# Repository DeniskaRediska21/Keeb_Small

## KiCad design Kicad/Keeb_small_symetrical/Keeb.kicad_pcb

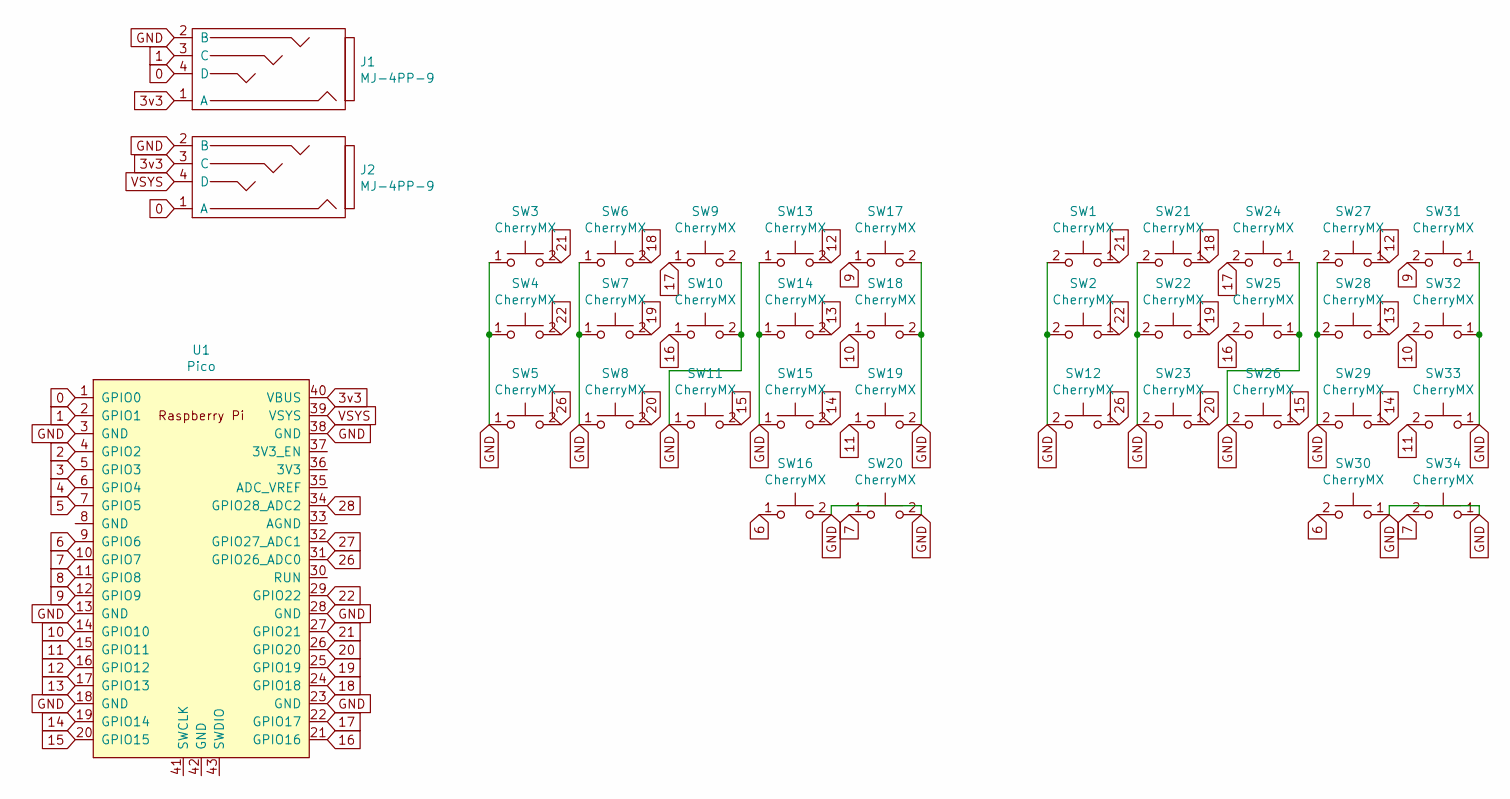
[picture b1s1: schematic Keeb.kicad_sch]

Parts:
J1, J2: MJ-4PP-9
SW1, SW2, SW3, SW4, SW5, SW6, SW7, SW8, SW9, SW10, SW11, SW12, SW13, SW14, SW15, SW16, SW17, SW18, SW19, SW20, SW21, SW22, SW23, SW24, SW25, SW26, SW27, SW28, SW29, SW30, SW31, SW32, SW33, SW34: CherryMX; MX_PCB_1.00u
U1: Pico; RPi_Pico_SMD_TH

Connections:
0: J1.4 (D), J2.1 (A), U1.1 (GPIO0)
1: J1.3 (C), U1.2 (GPIO1)
2: U1.4 (GPIO2)
3: U1.5 (GPIO3)
3v3: J1.1 (A), J2.3 (C), U1.40 (VBUS)
4: U1.6 (GPIO4)
5: U1.7 (GPIO5)
6: SW16.1, SW30.2, U1.9 (GPIO6)
7: SW20.1, SW34.2, U1.10 (GPIO7)
8: U1.11 (GPIO8)
9: SW17.1, SW31.2, U1.12 (GPIO9)
10: SW18.1, SW32.2, U1.14 (GPIO10)
11: SW19.1, SW33.2, U1.15 (GPIO11)
12: SW13.2, SW27.1, U1.16 (GPIO12)
13: SW14.2, SW28.1, U1.17 (GPIO13)
14: SW15.2, SW29.1, U1.19 (GPIO14)
15: SW11.2, SW26.1, U1.20 (GPIO15)
16: SW10.1, SW25.2, U1.21 (GPIO16)
17: SW9.1, SW24.2, U1.22 (GPIO17)
18: SW6.2, SW21.1, U1.24 (GPIO18)
19: SW7.2, SW22.1, U1.25 (GPIO19)
20: SW8.2, SW23.1, U1.26 (GPIO20)
21: SW1.1, SW3.2, U1.27 (GPIO21)
22: SW2.1, SW4.2, U1.29 (GPIO22)
26: SW5.2, SW12.1, U1.31 (GPIO26_ADC0)
27: U1.32 (GPIO27_ADC1)
28: U1.34 (GPIO28_ADC2)
GND: J1.2 (B), J2.2 (B), SW1.2, SW2.2, SW3.1, SW4.1, SW5.1, SW6.1, SW7.1, SW8.1, SW9.2, SW10.2, SW11.1, SW12.2, SW13.1, SW14.1, SW15.1, SW16.2, SW17.2, SW18.2, SW19.2, SW20.2, SW21.2, SW22.2, SW23.2, SW24.1, SW25.1, SW26.2, SW27.2, SW28.2, SW29.2, SW30.1, SW31.1, SW32.1, SW33.1, SW34.1, U1.3 (GND), U1.13 (GND), U1.18 (GND), U1.23 (GND), U1.28 (GND), U1.38 (GND)
VSYS: J2.4 (D), U1.39 (VSYS)

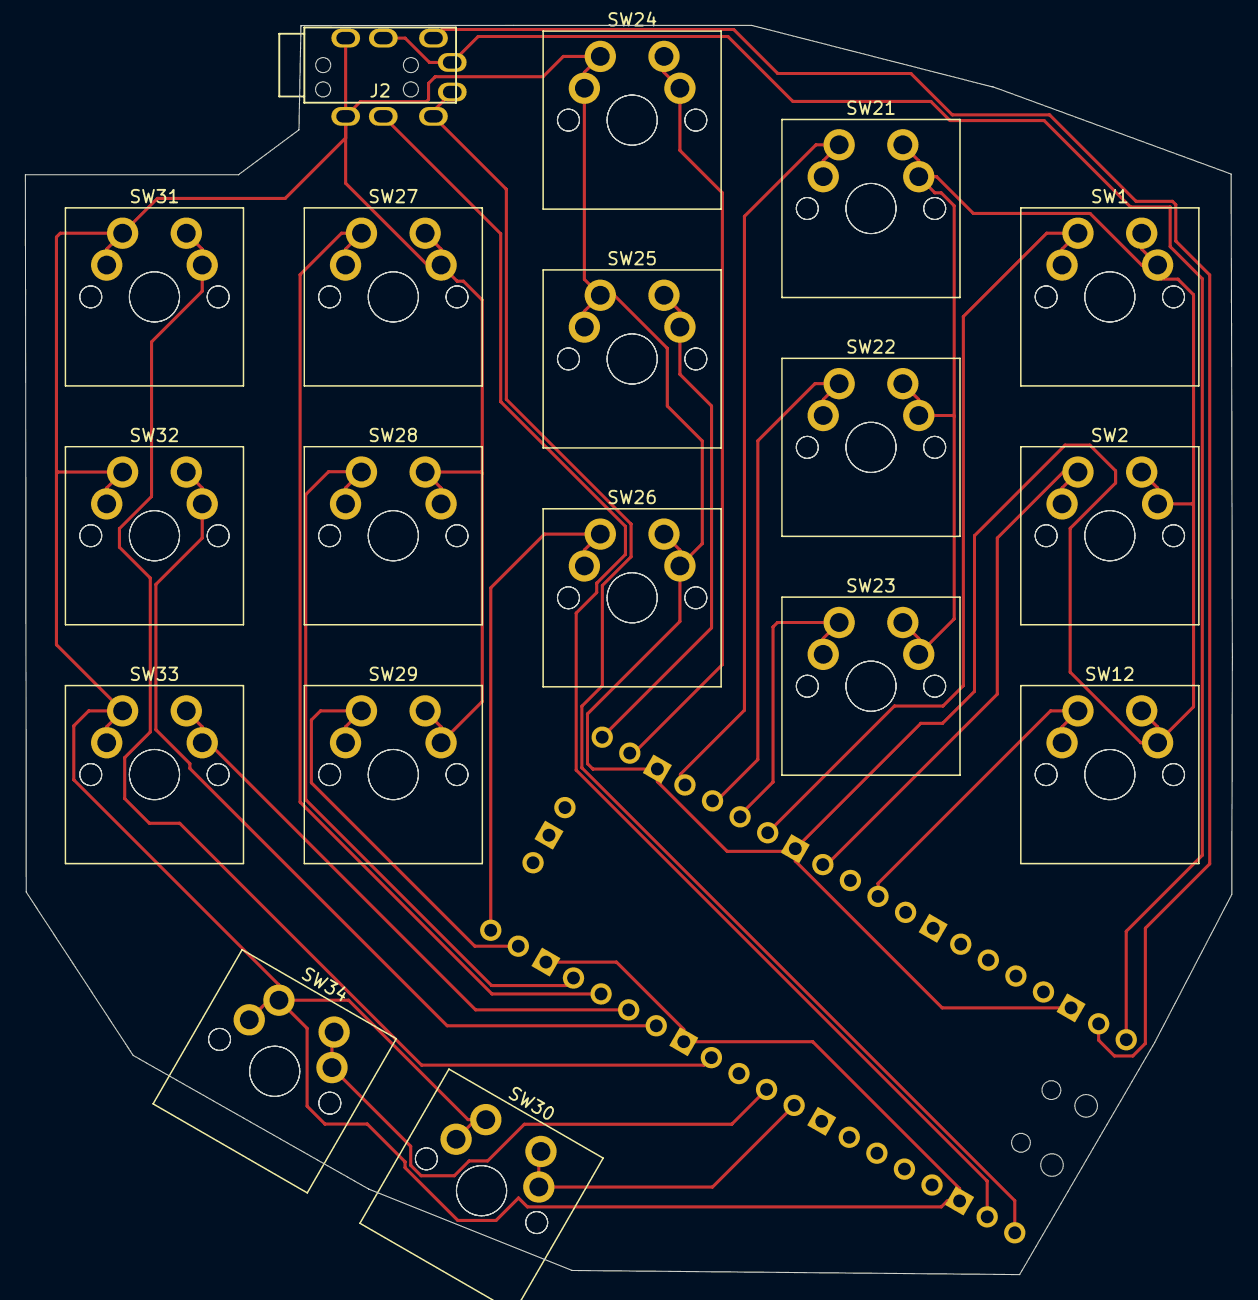
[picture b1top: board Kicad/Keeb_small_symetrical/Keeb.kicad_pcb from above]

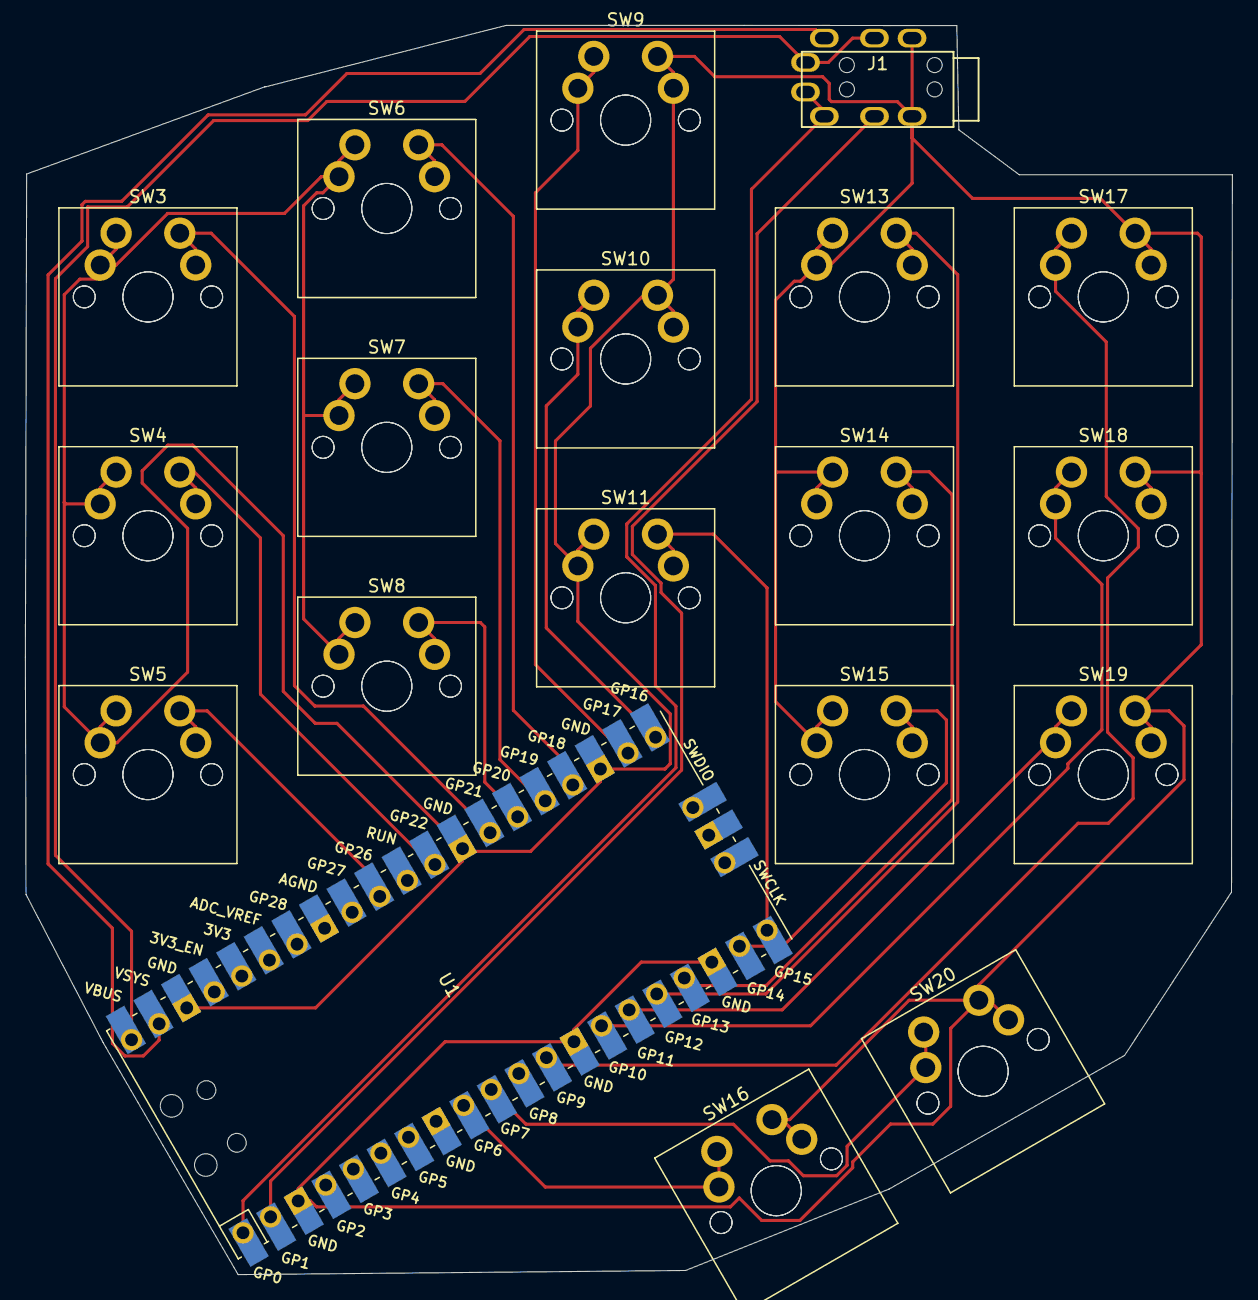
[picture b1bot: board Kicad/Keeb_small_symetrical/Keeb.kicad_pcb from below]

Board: 2 copper layers, 96.3 x 99.6 mm, 37 parts (19 on the bottom side), 22 nets.

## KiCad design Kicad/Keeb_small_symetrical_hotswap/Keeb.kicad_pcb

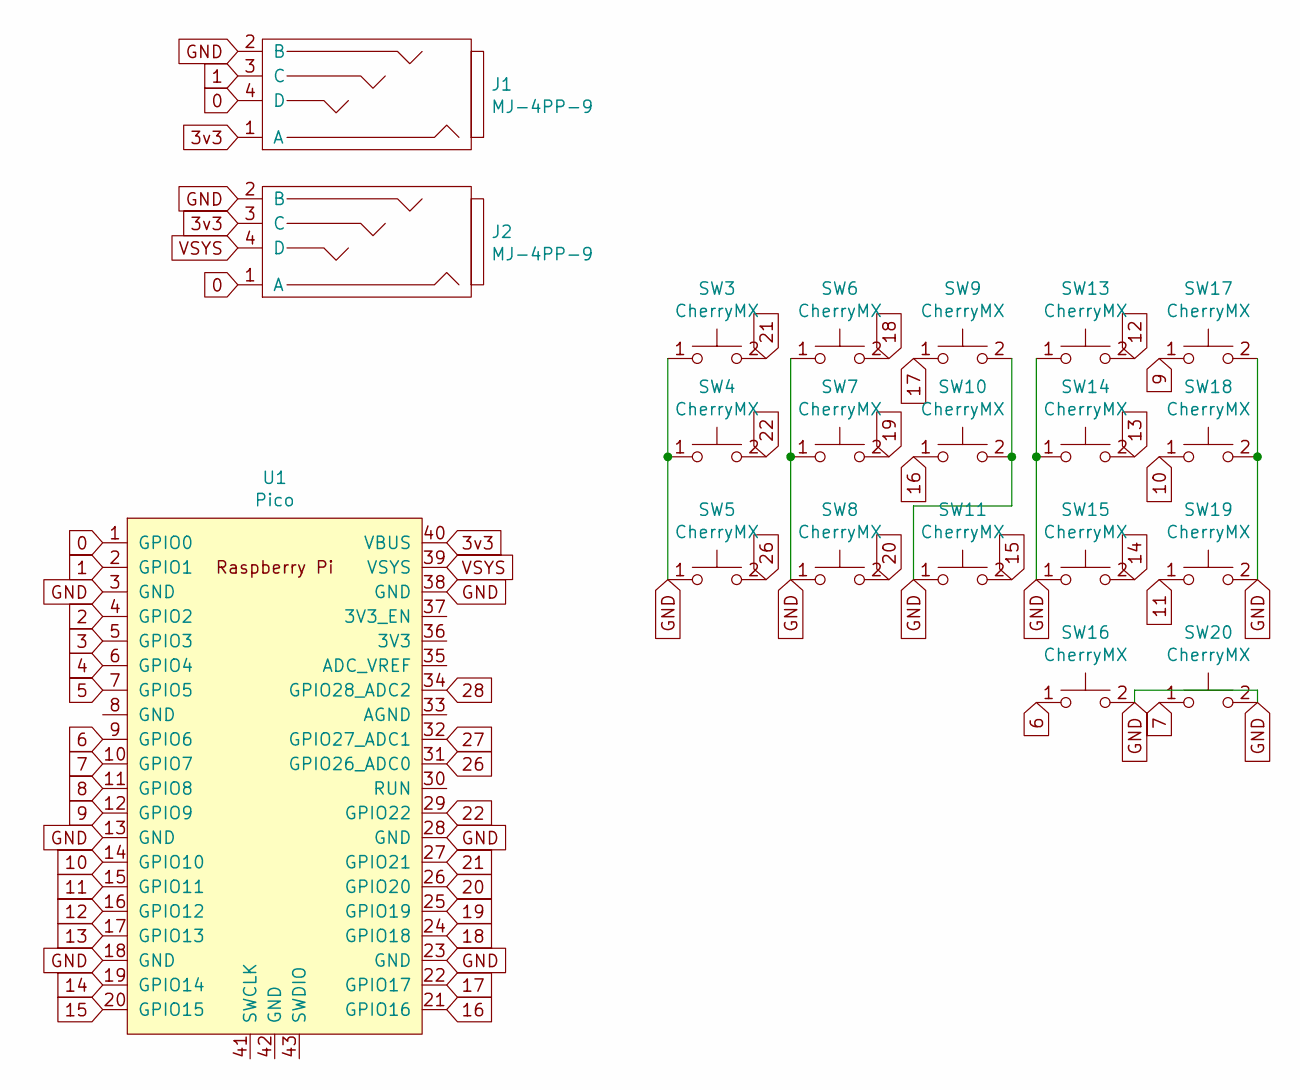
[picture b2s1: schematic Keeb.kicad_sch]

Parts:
J1, J2: MJ-4PP-9
SW3, SW4, SW5, SW6, SW7, SW8, SW9, SW10, SW11, SW13, SW14, SW15, SW16, SW17, SW18, SW19, SW20: CherryMX; Hotswap_MX_1.00u
U1: Pico; RPi_Pico_SMD_TH

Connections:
0: J1.4 (D), J2.1 (A), U1.1 (GPIO0)
1: J1.3 (C), U1.2 (GPIO1)
2: U1.4 (GPIO2)
3: U1.5 (GPIO3)
3v3: J1.1 (A), J2.3 (C), U1.40 (VBUS)
4: U1.6 (GPIO4)
5: U1.7 (GPIO5)
6: SW16.1, U1.9 (GPIO6)
7: SW20.1, U1.10 (GPIO7)
8: U1.11 (GPIO8)
9: SW17.1, U1.12 (GPIO9)
10: SW18.1, U1.14 (GPIO10)
11: SW19.1, U1.15 (GPIO11)
12: SW13.2, U1.16 (GPIO12)
13: SW14.2, U1.17 (GPIO13)
14: SW15.2, U1.19 (GPIO14)
15: SW11.2, U1.20 (GPIO15)
16: SW10.1, U1.21 (GPIO16)
17: SW9.1, U1.22 (GPIO17)
18: SW6.2, U1.24 (GPIO18)
19: SW7.2, U1.25 (GPIO19)
20: SW8.2, U1.26 (GPIO20)
21: SW3.2, U1.27 (GPIO21)
22: SW4.2, U1.29 (GPIO22)
26: SW5.2, U1.31 (GPIO26_ADC0)
27: U1.32 (GPIO27_ADC1)
28: U1.34 (GPIO28_ADC2)
GND: J1.2 (B), J2.2 (B), SW3.1, SW4.1, SW5.1, SW6.1, SW7.1, SW8.1, SW9.2, SW10.2, SW11.1, SW13.1, SW14.1, SW15.1, SW16.2, SW17.2, SW18.2, SW19.2, SW20.2, U1.3 (GND), U1.13 (GND), U1.18 (GND), U1.23 (GND), U1.28 (GND), U1.38 (GND)
VSYS: J2.4 (D), U1.39 (VSYS)

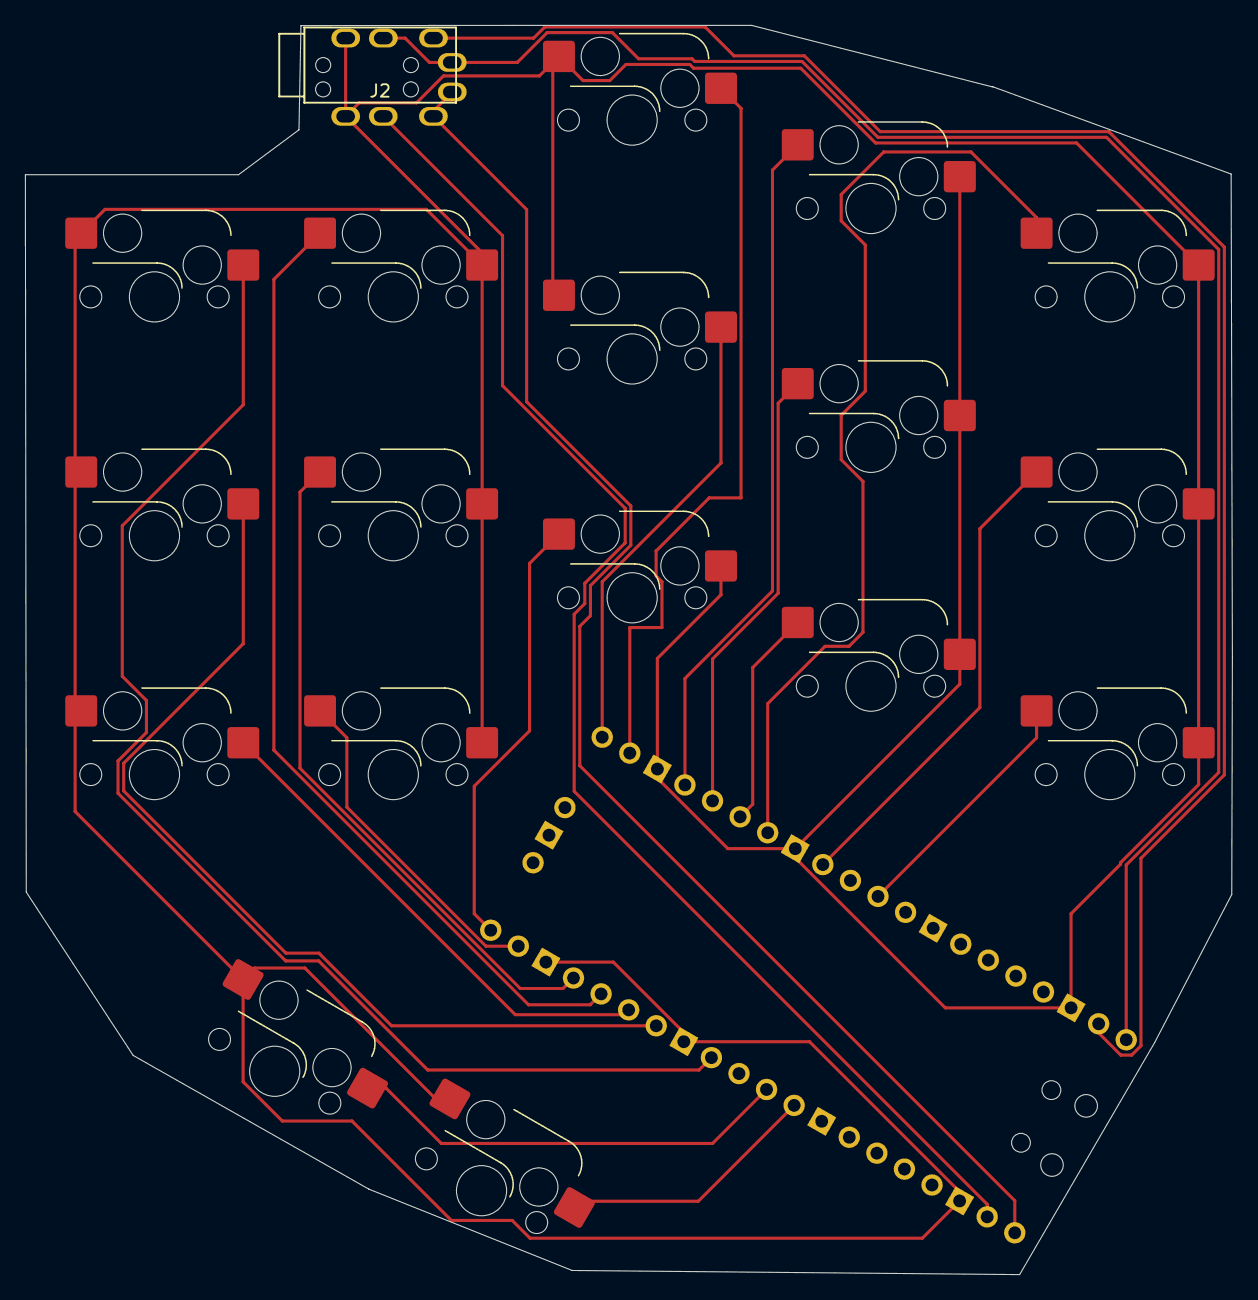
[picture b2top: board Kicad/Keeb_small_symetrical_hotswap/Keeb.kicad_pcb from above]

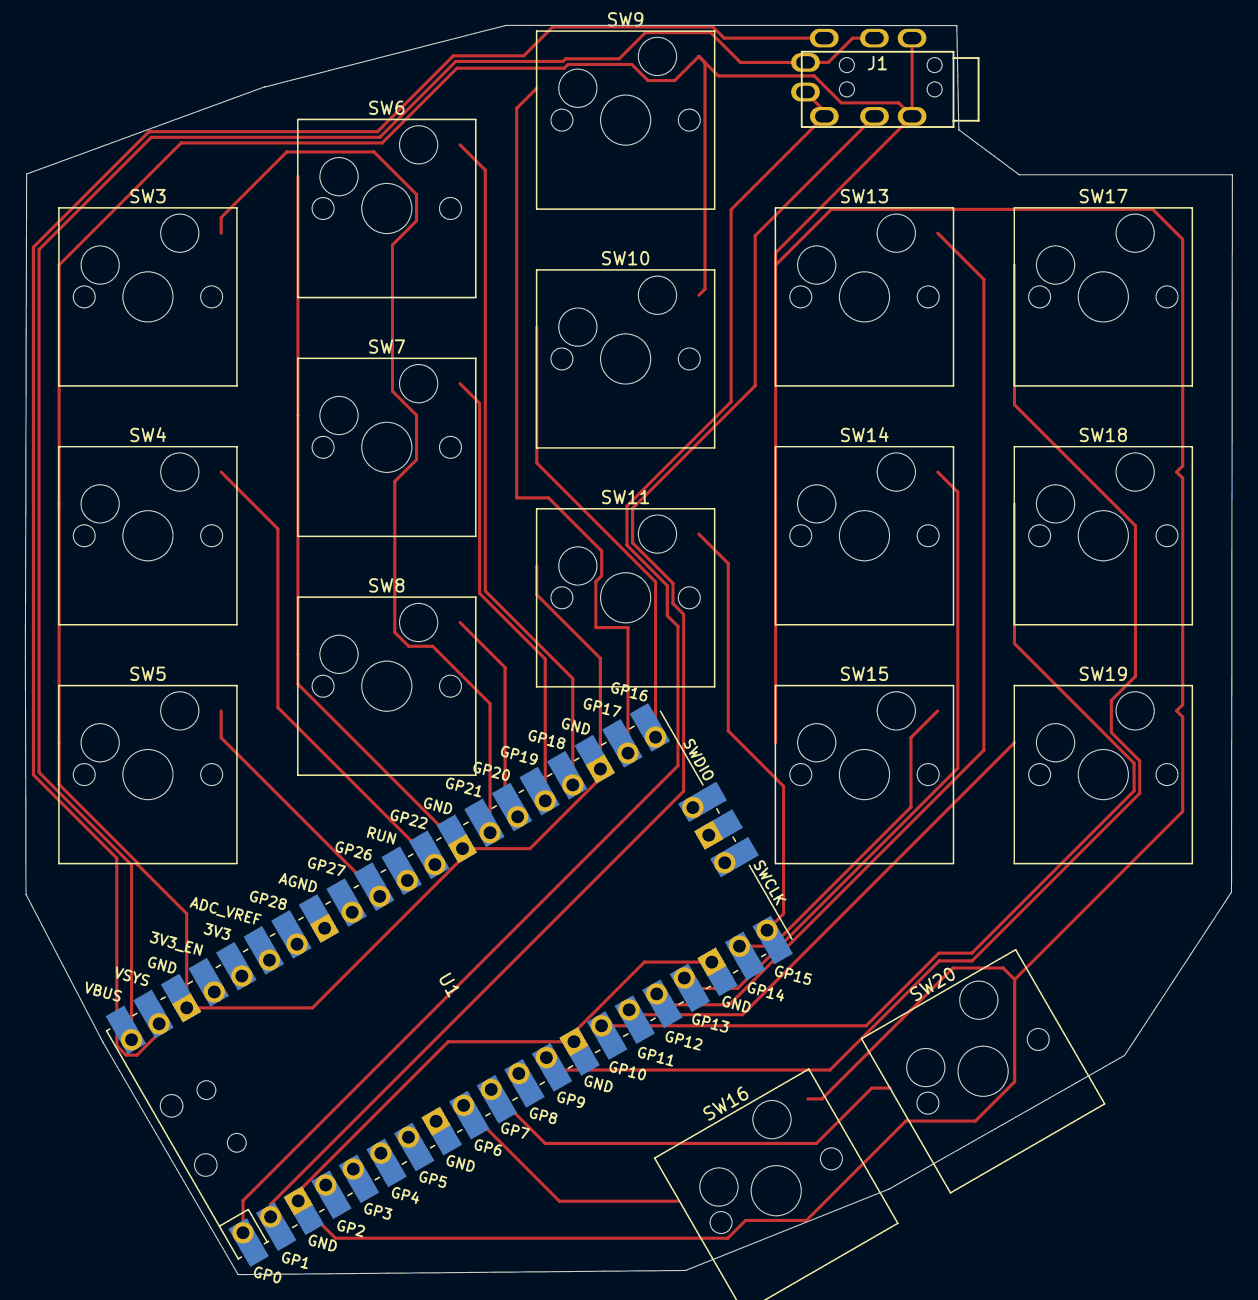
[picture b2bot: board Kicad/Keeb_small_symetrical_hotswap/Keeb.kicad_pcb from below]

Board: 2 copper layers, 96.3 x 99.6 mm, 20 parts (19 on the bottom side), 22 nets.

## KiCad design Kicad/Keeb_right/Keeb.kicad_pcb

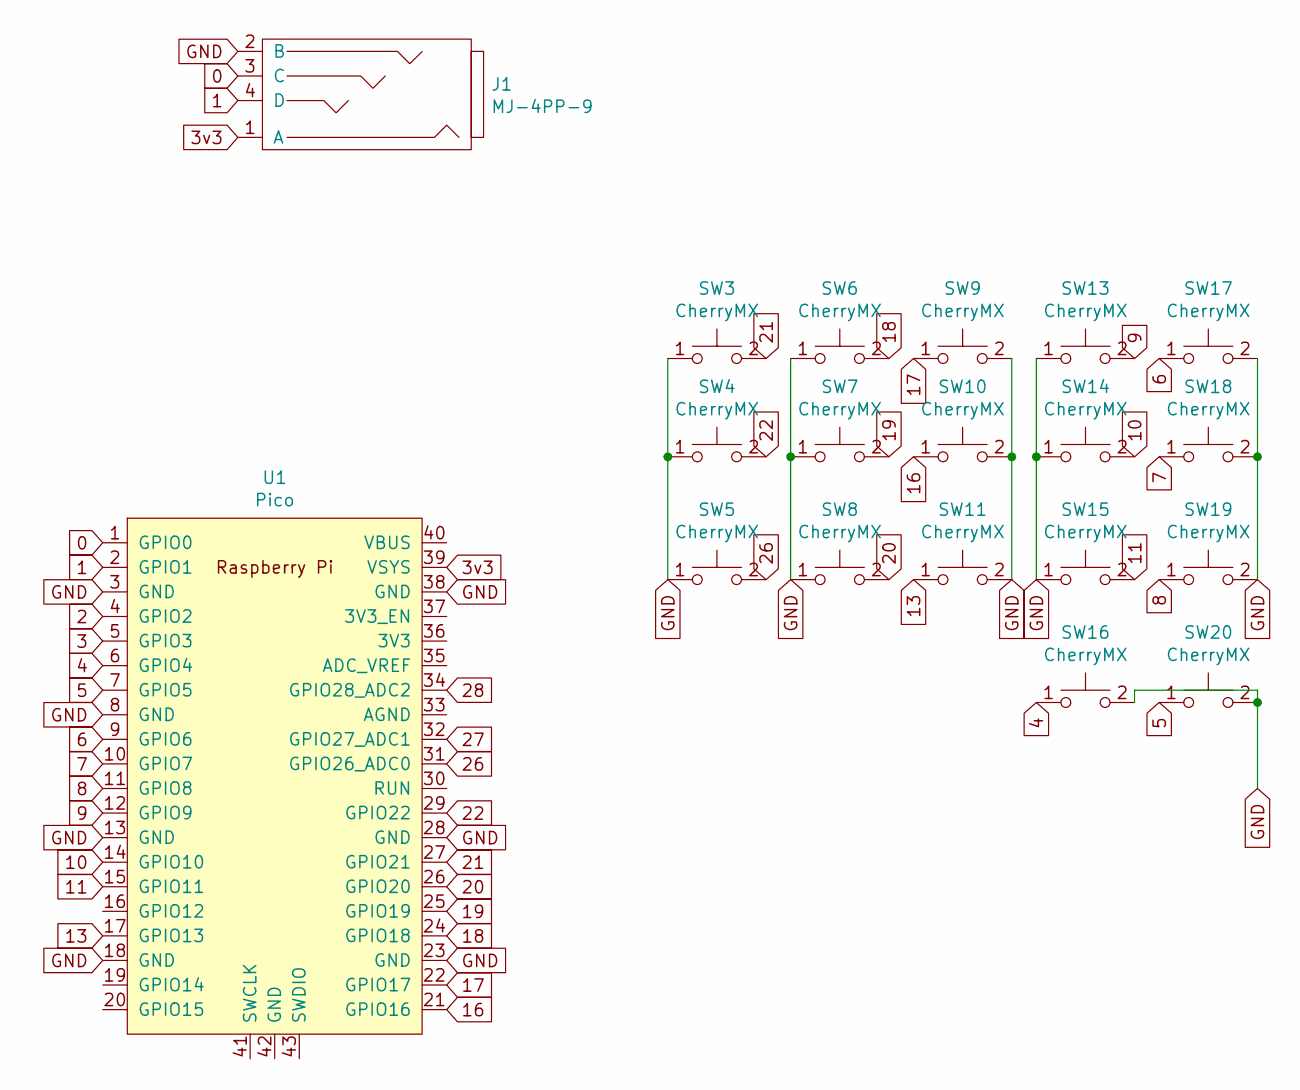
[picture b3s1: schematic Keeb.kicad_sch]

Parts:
J1: MJ-4PP-9; MJ-4PP-9_no_silk
SW3, SW4, SW5, SW6, SW7, SW8, SW9, SW10, SW11, SW13, SW14, SW15, SW16, SW17, SW18, SW19, SW20: CherryMX; MX_PCB_1.00u
U1: Pico; RPi_Pico_SMD_TH

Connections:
0: J1.3 (C), U1.1 (GPIO0)
1: J1.4 (D), U1.2 (GPIO1)
2: U1.4 (GPIO2)
3: U1.5 (GPIO3)
3v3: J1.1 (A), U1.39 (VSYS)
4: SW16.1, U1.6 (GPIO4)
5: SW20.1, U1.7 (GPIO5)
6: SW17.1, U1.9 (GPIO6)
7: SW18.1, U1.10 (GPIO7)
8: SW19.1, U1.11 (GPIO8)
9: SW13.2, U1.12 (GPIO9)
10: SW14.2, U1.14 (GPIO10)
11: SW15.2, U1.15 (GPIO11)
13: SW11.1, U1.17 (GPIO13)
16: SW10.1, U1.21 (GPIO16)
17: SW9.1, U1.22 (GPIO17)
18: SW6.2, U1.24 (GPIO18)
19: SW7.2, U1.25 (GPIO19)
20: SW8.2, U1.26 (GPIO20)
21: SW3.2, U1.27 (GPIO21)
22: SW4.2, U1.29 (GPIO22)
26: SW5.2, U1.31 (GPIO26_ADC0)
27: U1.32 (GPIO27_ADC1)
28: U1.34 (GPIO28_ADC2)
GND: J1.2 (B), SW3.1, SW4.1, SW5.1, SW6.1, SW7.1, SW8.1, SW9.2, SW10.2, SW11.2, SW13.1, SW14.1, SW15.1, SW16.2, SW17.2, SW18.2, SW19.2, SW20.2, U1.3 (GND), U1.8 (GND), U1.13 (GND), U1.18 (GND), U1.23 (GND), U1.28 (GND), U1.38 (GND)

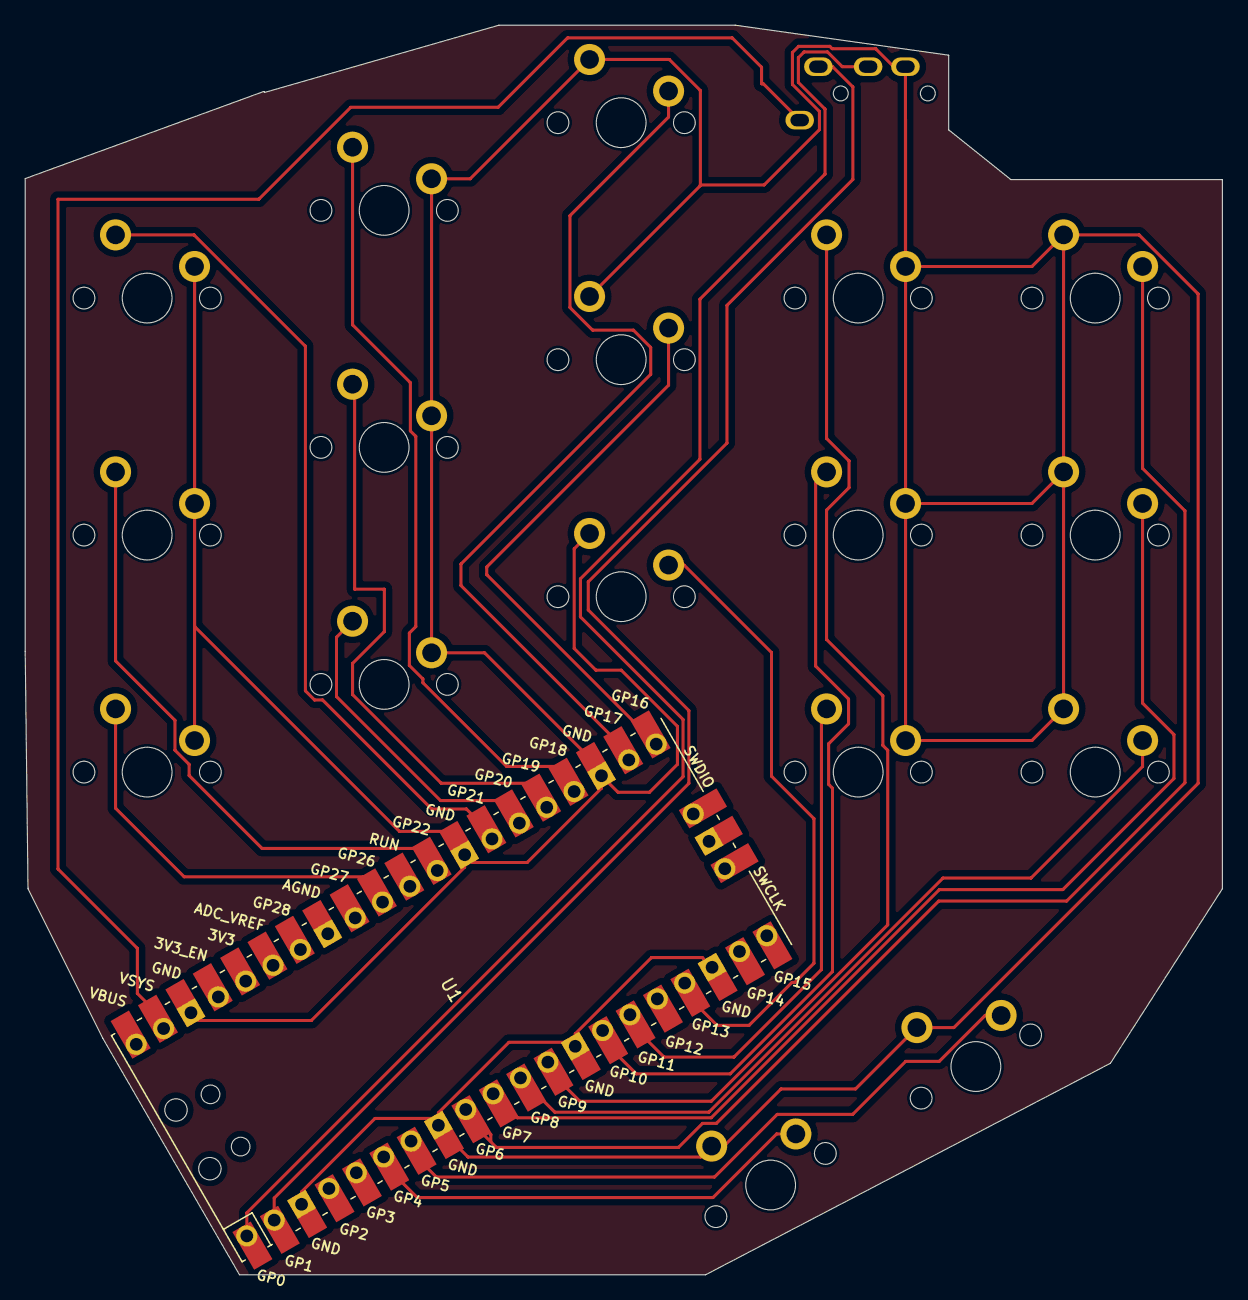
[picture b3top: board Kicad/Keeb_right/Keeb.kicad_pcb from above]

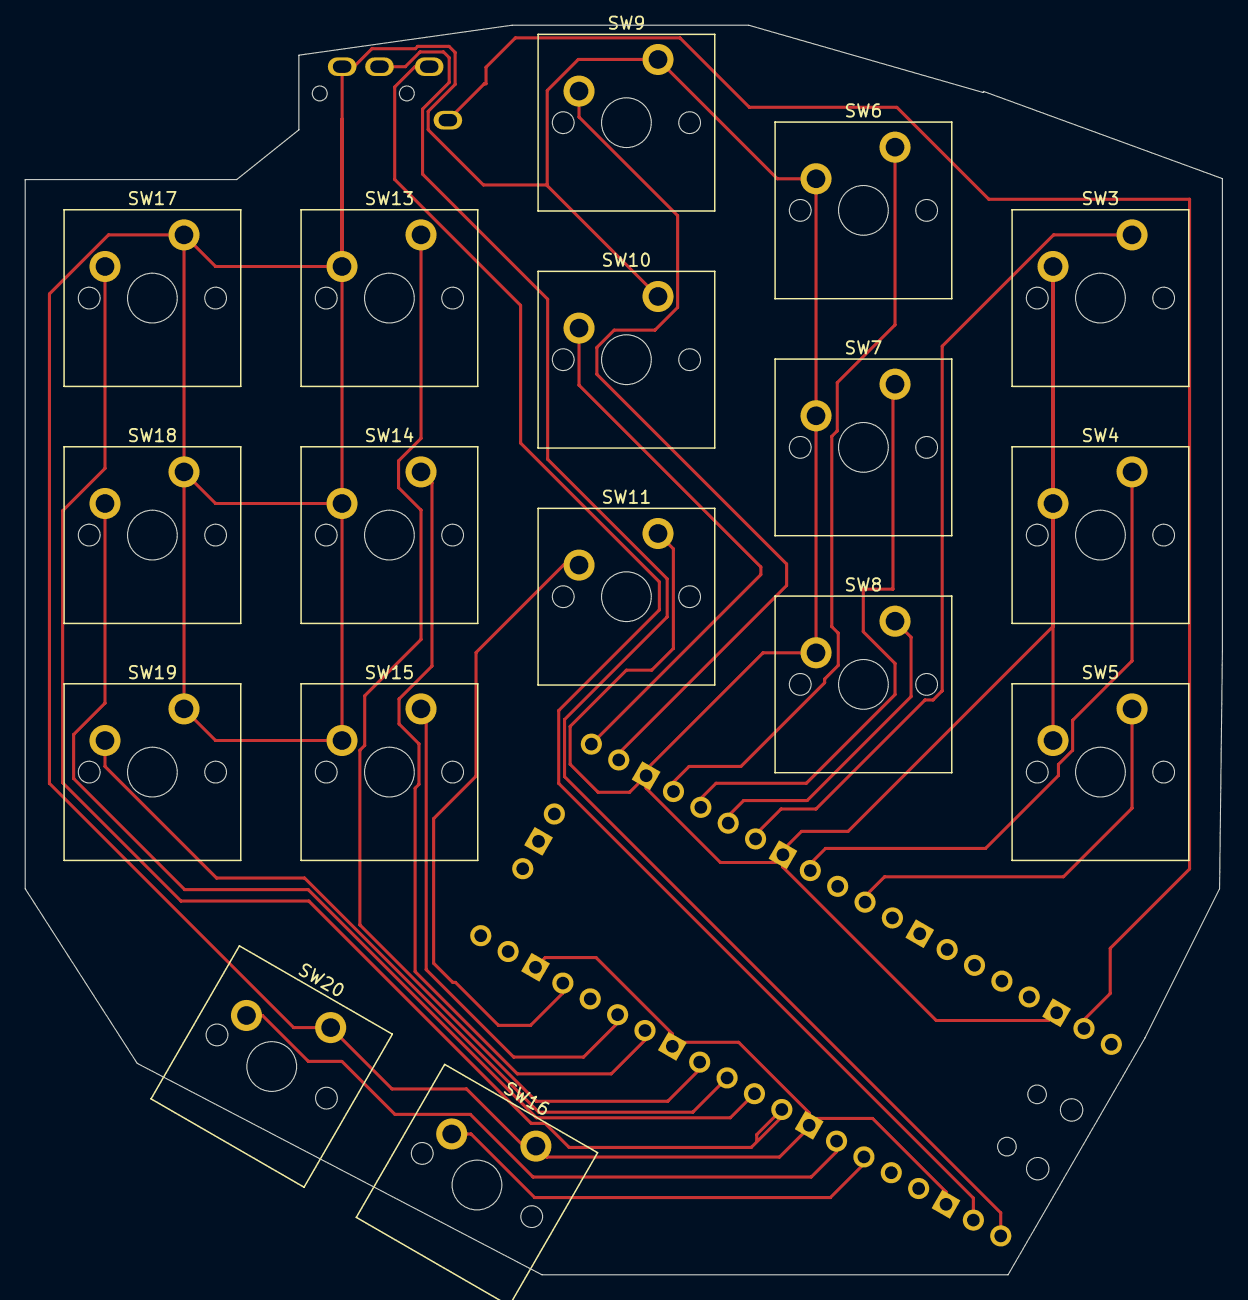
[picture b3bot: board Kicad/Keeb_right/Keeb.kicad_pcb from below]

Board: 2 copper layers, 96.2 x 100.4 mm, 19 parts (18 on the bottom side), 21 nets.

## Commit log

2023-10-30 Added universal left-right pcb design, started work on hotswap variant
2023-11-24 Finally added software
2023-11-25 changed keys
2023-11-25 keymappings
2023-11-28 Added Ctrl/Shift + Insert into Lower, added Ctrl + Alt + T to Lower
2023-11-28 moved some keys
2023-11-28 Added questionmark sign
2024-01-17 Update main.py
    Plug usb into any half
